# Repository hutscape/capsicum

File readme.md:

# Capsicum

> 🫑 Retrofit a wired doorbell to add WiFi and make it smart 🔔

Visit [hutscape.com/capsicum](https://hutscape.com/capsicum) for more details.

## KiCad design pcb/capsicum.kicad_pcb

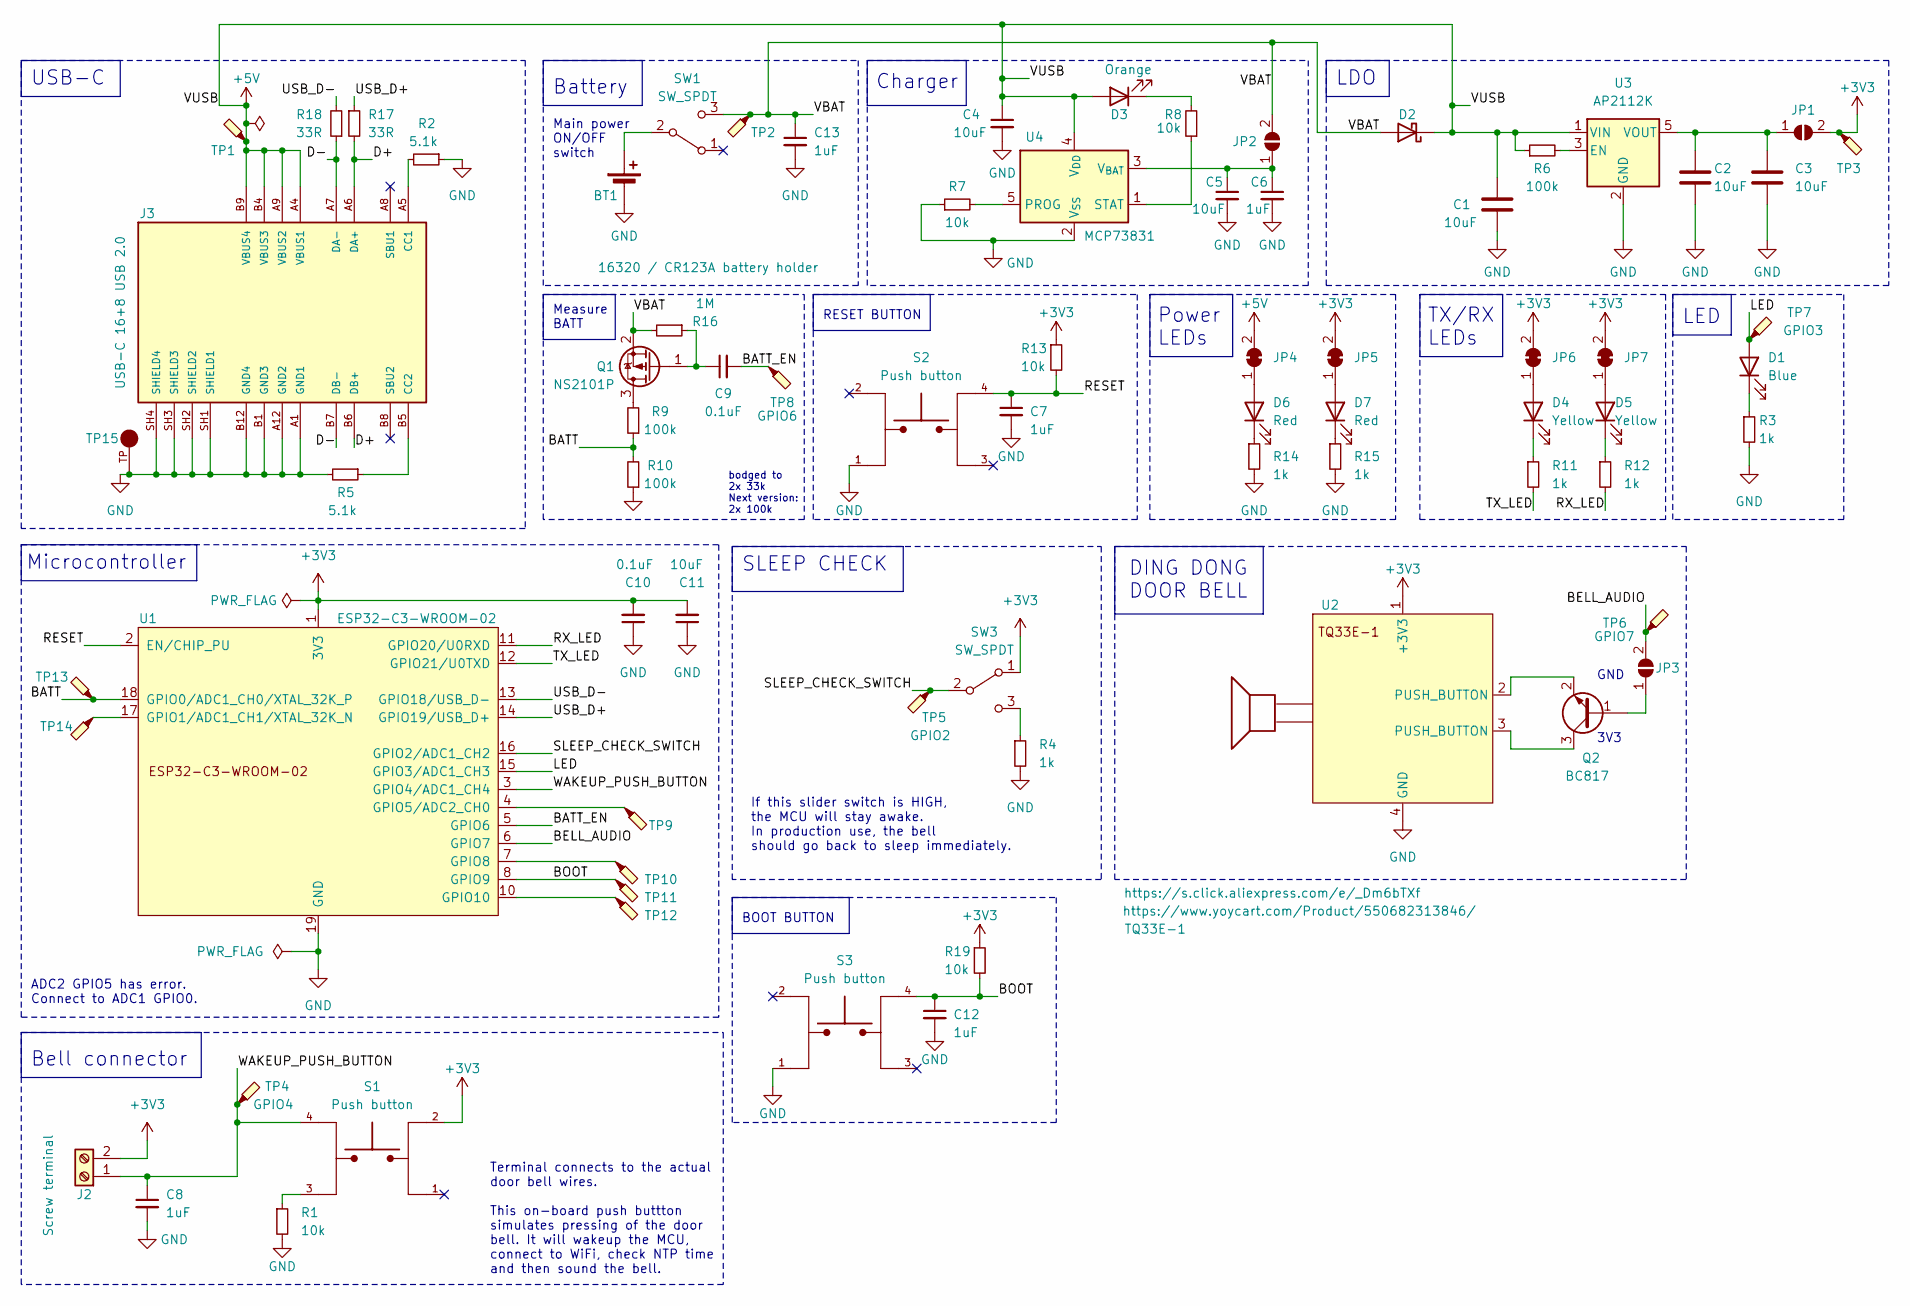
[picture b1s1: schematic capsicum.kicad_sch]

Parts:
BT1: 16320 / CR123A battery holder; CR123_holder
C1, C2, C3, C4, C5, C11: 10uF; C_0603_1608Metric; MPN CC0603KRX5R6BB106
C6, C7, C8, C12, C13: 1uF; C_0603_1608Metric; MPN 06033D105MAT2A
C9, C10: 0.1uF; C_0603_1608Metric; MPN 06033C104KAT4A
D1: Blue; D_0603_1608Metric; MPN 150060BS75000
D2: D_Schottky; D_SOD-123F; MPN PMEG3020EH,115
D3: Orange; D_0603_1608Metric; MPN B1911UD--20D001014U1930
D4, D5: Yellow; D_0603_1608Metric; MPN 150060YS75000
D6, D7: Red; D_0603_1608Metric; MPN 150060RS75000
J2: Screw terminal; phoenix_screw_terminal_th_1935161; MPN 1935161
J3: USB-C 16+8 USB 2.0; Molex_USB_C_2137160001; PARTREV B
JP1, JP2, JP3: SolderJumper_2_Open; PinHeader_1x02_P2.54mm_Vertical; MPN 61300211121
JP4, JP5, JP6, JP7: SolderJumper_2_Bridged; SolderJumper-2_P1.3mm_Bridged_RoundedPad1.0x1.5mm
Q1: NS2101P; SOT-323_SC-70; MPN NTS2101PT1G
Q2: BC817; SOT-23-3; MPN BC817-16LT3G
R1, R7, R8, R13, R19: 10k; R_0603_1608Metric; MPN RC0603FR-0710KL
R2, R5: 5.1k; R_0603_1608Metric; MPN ERJ-3GEYJ512V
R3, R4, R11, R12, R14, R15: 1k; R_0603_1608Metric; MPN RC0603FR-071KL
R6, R9, R10: 100k; R_0603_1608Metric; MPN RMCF0603FT100K
R16: 1M; R_0603_1608Metric; MPN RC0603FR-071ML
R17, R18: 33R; R_0603_1608Metric; MPN RC0603JR-0733RL
S1, S2, S3: Push button; SW_TL3305AF160QG; PARTREV C
SW1: SW_SPDT; SW_SPDT_PCM12; MPN CUS-12TB
SW3: SW_SPDT; SW_JS102011JCQN; MPN JS102011JCQN
TP1, TP2, TP3, TP4, TP5, TP6, TP7, TP8, TP9, TP10, TP11, TP12, TP13, TP14: TestPoint_Probe; TestPoint_Pad_1.5x1.5mm
TP15: 5015; Keystone_test_point_5015; MPN 5015
U1: ESP32-C3-WROOM-02; MPN ESP32-C3-WROOM-02-N4
U2: R/A 4x1 2.54mm pin header; PinHeader_1x04_P2.54mm_Horizontal; MPN PH1RB-04-UA
U3: AP2112K; SOT-23-5; MPN AP2112K-3.3TRG1
U4: MCP73831; SOT-23-5; MPN MCP73831T-2ACI/OT

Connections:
+3V3: C10.2, C11.2, J2.2, JP1.2 (B), JP5.2 (B), JP6.2 (B), JP7.2 (B), R13.1, R19.1, S1.2, SW3.1 (A), TP3.1, U1.1 (3V3), U2.1 (+3V3)
+5V: C1.1, C4.1, D2.1 (K), D3.2 (A), J3.A4 (VBUS1), J3.A9 (VBUS2), J3.B4 (VBUS3), J3.B9 (VBUS4), JP4.2 (B), R6.1, TP1.1, U3.1 (VIN), U4.4 (V_{DD})
/BATT: R9.1, R10.2, TP13.1, U1.18 (GPIO0/ADC1_CH0/XTAL_32K_P)
/BATT_EN: C9.2, TP8.1, U1.5 (GPIO6)
/BELL_AUDIO: JP3.2 (B), TP6.1, U1.6 (GPIO7)
/BOOT: C12.1, R19.2, S3.4, TP11.1, U1.8 (GPIO9)
/D+: J3.A6 (DA+), J3.B6 (DB+), R17.2
/D-: J3.A7 (DA-), J3.B7 (DB-), R18.1
/LED: D1.2 (A), TP7.1, U1.15 (GPIO3/ADC1_CH3)
/RESET: C7.1, R13.2, S2.4, U1.2 (EN/CHIP_PU)
/RX_LED: R12.2, U1.11 (GPIO20/U0RXD)
/SLEEP_CHECK_SWITCH: SW3.2 (B), TP5.1, U1.16 (GPIO2/ADC1_CH2)
/TX_LED: R11.2, U1.12 (GPIO21/U0TXD)
/USB_D+: R17.1, U1.14 (GPIO19/USB_D+)
/USB_D-: R18.2, U1.13 (GPIO18/USB_D-)
/VBAT: C13.1, D2.2 (A), JP2.2 (B), Q1.2 (S), R16.2, SW1.3 (C), TP2.1
/WAKEUP_PUSH_BUTTON: C8.1, J2.1, S1.4, TP4.1, U1.3 (GPIO4/ADC1_CH4)
GND: BT1.2 (-), C1.2, C2.2, C3.2, C4.2, C5.2, C6.2, C7.2, C8.2, C10.1, C11.1, C12.2, C13.2, J3.A1 (GND1), J3.A12 (GND2), J3.B1 (GND3), J3.B12 (GND4), J3.SH1 (SHIELD1), J3.SH2 (SHIELD2), J3.SH3 (SHIELD3), J3.SH4 (SHIELD4), R1.2, R2.1, R3.2, R4.2, R5.2, R7.1, R10.1, R14.2, R15.2, S2.1, S3.1, TP15.TP, U1.9 (GND), U1.19 (GND), U2.4 (GND), U3.2 (GND), U4.2 (V_{SS})
unnamed: BT1.1 (+), SW1.2 (B)
unnamed: D1.1 (K), R3.1
unnamed: D3.1 (K), R8.2
unnamed: D4.2 (A), JP6.1 (A)
unnamed: D4.1 (K), R11.1
unnamed: D5.2 (A), JP7.1 (A)
unnamed: D5.1 (K), R12.1
unnamed: D6.2 (A), JP4.1 (A)
unnamed: D6.1 (K), R14.1
unnamed: D7.2 (A), JP5.1 (A)
unnamed: D7.1 (K), R15.1
unnamed: J3.A5 (CC1), R2.2
unnamed: J3.B5 (CC2), R5.1
unnamed: C2.1, C3.1, JP1.1 (A), U3.5 (VOUT)
unnamed: C5.1, C6.1, JP2.1 (A), U4.3 (V_{BAT})
unnamed: JP3.1 (A), Q2.1 (B)
unnamed: Q1.3 (D), R9.2
unnamed: C9.1, Q1.1 (G), R16.1
unnamed: Q2.3 (C), U2.3 (PUSH_BUTTON)
unnamed: Q2.2 (E), U2.2 (PUSH_BUTTON)
unnamed: R1.1, S1.3
unnamed: R4.1, SW3.3 (C)
unnamed: TP14.1, U1.17 (GPIO1/ADC1_CH1/XTAL_32K_N)
unnamed: TP9.1, U1.4 (GPIO5/ADC2_CH0)
unnamed: TP10.1, U1.7 (GPIO8)
unnamed: TP12.1, U1.10 (GPIO10)
unnamed: R6.2, U3.3 (EN)
unnamed: R7.2, U4.5 (PROG)
unnamed: R8.1, U4.1 (STAT)

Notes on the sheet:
LED
Terminal connects to the actual door bell wires. This on-board push buttton simulates pressing of the door bell. It will wakeup the MCU, connect to WiFi, check NTP time and then sound the bell.
TX/RX LEDs
bodged to 2x 33k Next version: 2x 100k
Main power ON/OFF switch
If this slider switch is HIGH, the MCU will stay awake. In production use, the bell should go back to sleep immediately.
3V3
Measure BATT
SLEEP CHECK
ADC2 GPIO5 has error. Connect to ADC1 GPIO0.
RESET BUTTON
Charger
BOOT BUTTON
USB-C
Bell connector
DING DONG DOOR BELL
Microcontroller
GND
Power LEDs
Battery
LDO

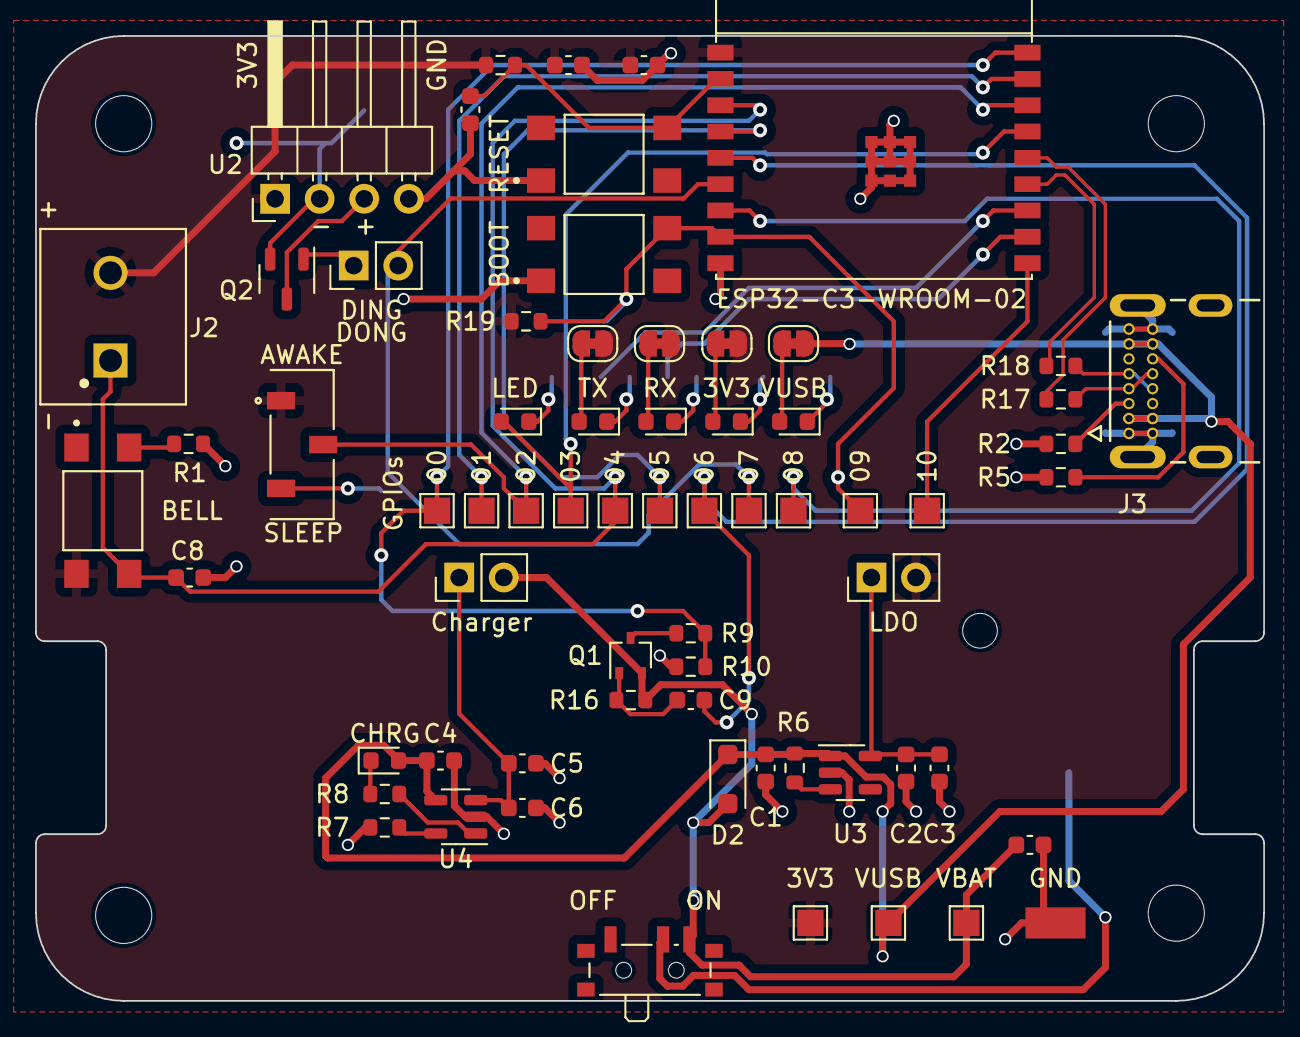
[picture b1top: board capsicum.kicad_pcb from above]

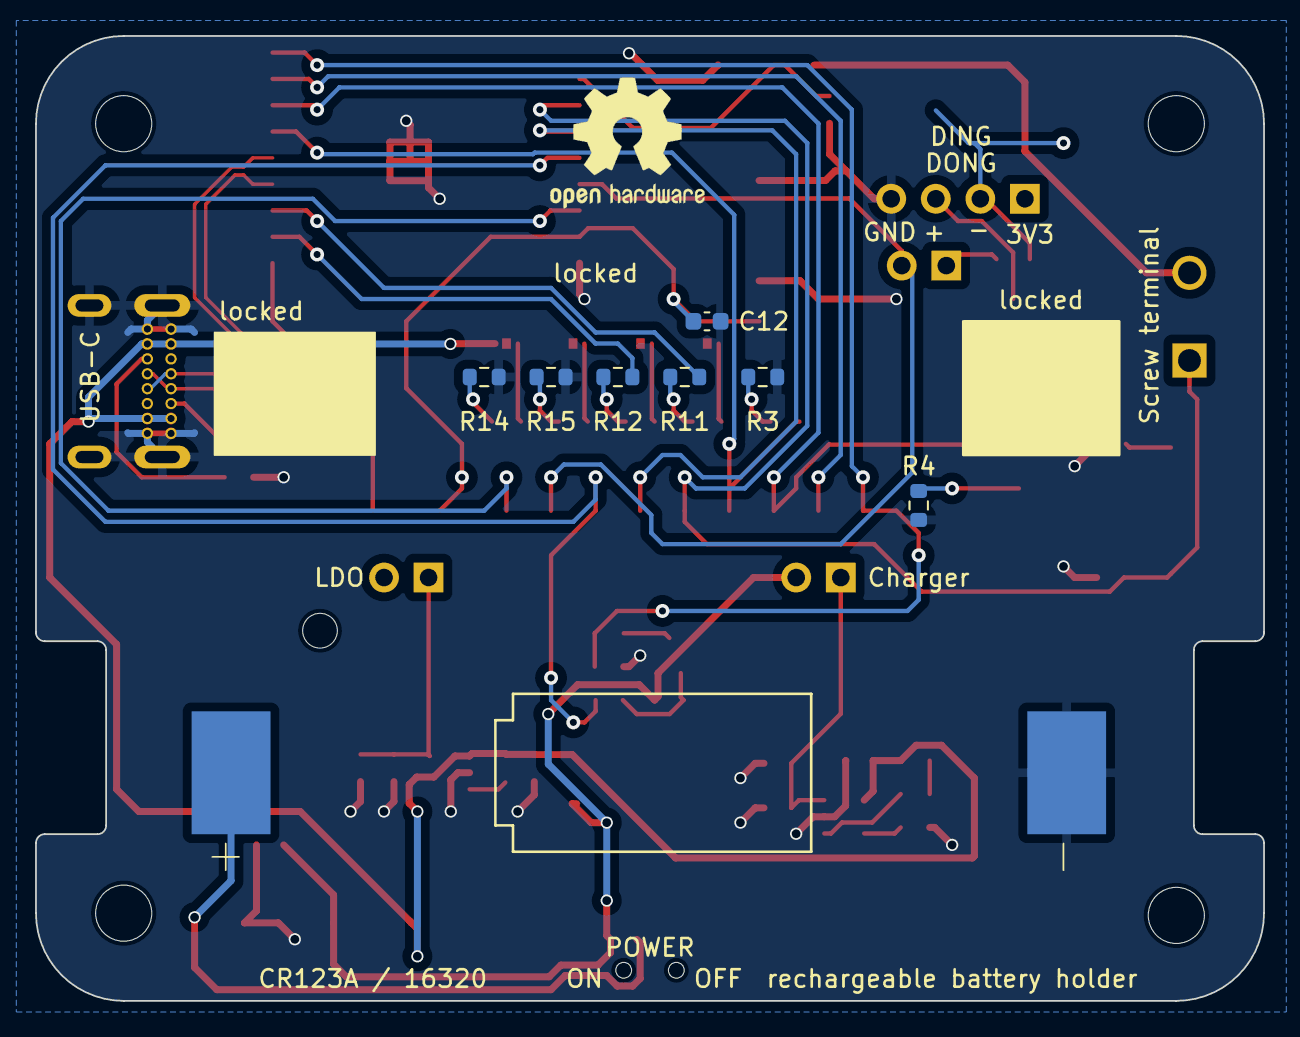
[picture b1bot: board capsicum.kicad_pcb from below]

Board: 2 copper layers, 70.0 x 55.0 mm, 75 parts (8 on the bottom side), 47 nets.

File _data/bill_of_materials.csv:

Designator,Value,Qty,Package,Category,Manufacturer,MPN,Datasheet,Vendor,Link,Unit,Total,Description,DNP
BT1,16320 / CR123A battery holder,1,SMD,Connector,EAEONXE,,https://www.aliexpress.com/item/1005004821679671.html,AliExpress,https://s.click.aliexpress.com/e/_DBxLGXX,2.2200,2.2200,Battery Holder CR123A:CR123_holder,
"C1-C5, C11",10uF,6,0603,Electronics,YAGEO,CC0603KRX5R6BB106,https://www.yageo.com/upload/website/yageo_High%20Capacitanc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,PCBWay,https://www.digikey.sg/en/products/detail/yageo/CC0603KRX5R6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,0.0284,0.1704,Capacitor_SMD:C_0603_1608Metric,
"C6-C8, C12, C13",1uF,5,0603,Electronics,Kyocera,06033D105MAT2A,https://datasheets.kyocera-avx.com/cx5r.pdf,PCBWay,https://www.digikey.co.nz/en/products/detail/kyocera-avx/KGM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,0.1748,0.8740,Capacitor_SMD:C_0603_1608Metric,
"C9, C10",0.1uF,2,0603,Electronics,Kyocera,06033C104KAT4A,https://datasheets.kyocera-avx.com/X7RDielectric.pdf,PCBWay,https://www.digikey.ca/en/products/detail/kyocera-avx/KGM15B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,0.1028,0.2056,Capacitor_SMD:C_0603_1608Metric,
D1,Blue,1,0603,Electronics,Würth Elektronik,150060BS75000,https://www.we-online.com/components/products/datasheet/1500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,PCBWay,https://www.digikey.sg/en/products/detail/w%C3%BCrth-elektro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,0.1970,0.1970,Diode_SMD:D_0603_1608Metric,
D2,D_Schottky,1,SOD-123F,Electronics,Nexperia USA Inc.,"PMEG3020EH,115",https://assets.nexperia.com/documents/data-sheet/PMEG3020EH.pdf,PCBWay,https://www.digikey.sg/en/products/detail/nexperia-usa-inc/P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,0.5566,0.5566,Diode_SMD:D_SOD-123F,
D3,Orange,1,0603,Electronics,Harvatek Corporation,B1911UD--20D001014U1930,https://mm.digikey.com/Volume0/opasdata/d220001/medias/docus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,PCBWay,https://www.digikey.sg/en/products/detail/harvatek-corporati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,0.1199,0.1199,Diode_SMD:D_0603_1608Metric,
"D4, D5",Yellow,2,0603,Electronics,Würth Elektronik,150060YS75000,https://www.we-online.com/components/products/datasheet/1500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,PCBWay,https://www.digikey.sg/en/products/detail/w%C3%BCrth-elektro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,0.1790,0.3580,Diode_SMD:D_0603_1608Metric,
"D6, D7",Red,2,0603,Electronics,Würth Elektronik,150060RS75000,https://www.we-online.com/components/products/datasheet/1500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,PCBWay,https://www.digikey.sg/en/products/detail/w%C3%BCrth-elektro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,0.1790,0.3580,Diode_SMD:D_0603_1608Metric,
J2,Screw terminal,1,TH,Connector,Phoenix,1935161,https://media.digikey.com/pdf/Data%20Sheets/Phoenix%20Contac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,PCBWay,https://www.digikey.sg/en/products/detail/phoenix-contact/19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,0.2835,0.2835,Screw Terminal:phoenix_screw_terminal_th_1935161,
J3,USB-C 16+8 USB 2.0,1,TH,Connector,Molex,2137160001,https://www.molex.com/en-us/products/part-detail/2137160001,PCBWay,https://www.digikey.sg/en/products/detail/molex/2137160001/13662558,0.9651,0.9651,Molex_USB_C:Molex_USB_C_2137160001,
JP1-JP3,SolderJumper_2_Open,3,TH,Electronics,Würth Elektronik,61300211121,https://www.we-online.com/components/products/datasheet/6130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,PCBWay,https://www.digikey.sg/en/products/detail/w%C3%BCrth-elektro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,0.0945,0.2835,Connector_PinHeader_2.54mm:PinHeader_1x02_P2.54mm_Vertical,
JP4-JP7,SolderJumper_2_Bridged,4,,Electronics,,,,,,0.0000,0.0000,Jumper:SolderJumper-2_P1.3mm_Bridged_RoundedPad1.0x1.5mm,DNP all
Q1,NS2101P,1,SC-70-3 (SOT323),Electronics,OnSemi,NTS2101PT1G,https://www.onsemi.com/pdf/datasheet/nts2101p-d.pdf,PCBWay,https://www.digikey.sg/en/products/detail/onsemi/NTS2101PT1G/687099,0.4712,0.4712,Package_TO_SOT_SMD:SOT-323_SC-70,
Q2,BC817,1,SOT-23-3,Electronics,OnSemi,BC817-16LT3G,https://www.onsemi.com/pub/Collateral/BC818-D.pdf,PCBWay,https://www.digikey.sg/en/products/detail/onsemi/BC817-16LT3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,0.1593,0.1593,Package_TO_SOT_SMD:SOT-23-3,
"R1, R7, R8, R13, R19",10k,5,0603,Electronics,YAGEO,RC0603FR-0710KL,https://www.yageo.com/upload/media/product/productsearch/dat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,PCBWay,https://www.digikey.sg/en/products/detail/yageo/RC0603FR-071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,0.0038,0.0190,Resistor_SMD:R_0603_1608Metric,
"R2, R5",5.1k,2,0603,Electronics,Panasonic,ERJ-3GEYJ512V,https://industrial.panasonic.com/ww/products/pt/general-purp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,PCBWay,https://www.digikey.sg/en/products/detail/panasonic-electron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,0.1149,0.2298,Resistor_SMD:R_0603_1608Metric,
"R3, R4, R11, R12, R14, R15",1k,6,0603,Electronics,Yageo,RC0603FR-071KL,https://www.yageo.com/upload/media/product/productsearch/dat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,PCBWay,https://www.digikey.sg/en/products/detail/yageo/RC0603FR-071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,0.1149,0.6894,Resistor_SMD:R_0603_1608Metric,
"R6, R9, R10",100k,3,0603,Electronics,Stackpole,RMCF0603FT100K,https://www.seielect.com/Catalog/SEI-RMCF_RMCP.pdf,PCBWay,https://www.digikey.sg/en/products/detail/stackpole-electron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,0.1149,0.3447,Resistor_SMD:R_0603_1608Metric,
R16,1M,1,0603,Electronics,YAGEO,RC0603FR-071ML,https://www.yageo.com/upload/media/product/productsearch/dat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,PCBWay,https://www.digikey.sg/en/products/detail/yageo/RC0603FR-071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,0.0013,0.0013,Resistor_SMD:R_0603_1608Metric,
"R17, R18",33R,2,0603,Electronics,YAGEO,RC0603JR-0733RL,https://www.yageo.com/upload/media/product/productsearch/dat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,PCBWay,https://www.digikey.sg/en/products/detail/yageo/RC0603JR-073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,0.0208,0.0416,Resistor_SMD:R_0603_1608Metric,
S1-S3,Push button,3,SMD,Connector,E-Switch,TL3305AF160QG,https://sten-eswitch-13110800-production.s3.amazonaws.com/sy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,PCBWay,https://www.digikey.sg/en/products/detail/e-switch/TL3305AF1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,0.1701,0.5103,Push button:SW_TL3305AF160QG,
SW1,SW_SPDT,1,SMD,Electronics,Nidec Copal,CUS-12TB,https://www.nidec-components.com/e/catalog/switch/cus.pdf,PCBWay,https://www.digikey.sg/en/products/detail/nidec-copal-electr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,0.8033,0.8033,Button_Switch_SMD:SW_SPDT_PCM12,
SW3,SW_SPDT,1,SMD,Electronics,C&K,JS102011JCQN,https://www.ckswitches.com/media/1422/js.pdf,PCBWay,https://www.digikey.sg/en/products/detail/c-k/JS102011JCQN/6137628,0.7125,0.7125,Slide switch:SW_JS102011JCQN,
TP1-TP14,TestPoint_Probe,14,,Electronics,,,,,,0.0000,0.0000,TestPoint:TestPoint_Pad_1.5x1.5mm,DNP all
TP15,5015,1,SMD,Electronics,Keystone,5015,https://www.keyelco.com/userAssets/file/M65p55.pdf,PCBWay,https://www.digikey.sg/en/products/detail/keystone-electroni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,0.1418,0.1418,Keystone_TP:Keystone_test_point_5015,
U1,ESP32-C3-WROOM-02,1,SMD,Electronics,Espressif,ESP32-C3-WROOM-02-N4,https://www.espressif.com/sites/default/files/documentation/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,PCBWay,https://www.digikey.sg/en/products/detail/espressif-systems/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,2.6334,2.6334,Espressif:ESP32-C3-WROOM-02,
U2,R/A 4x1 2.54mm pin header,1,TH,Electronics,Adam Tech,PH1RB-04-UA,https://app.adam-tech.com/products/download/data_sheet/20128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,PCBWay,https://www.digikey.sg/en/products/detail/adam-tech/PH1RB-04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,0.2600,0.2600,Connector_PinHeader_2.54mm:PinHeader_1x04_P2.54mm_Horizontal,
U3,AP2112K,1,SOT-23-5 or SOT-753 or SOT-25,Electronics,Diodes Incorporated,AP2112K-3.3TRG1 ,https://www.diodes.com/assets/Datasheets/AP2112.pdf,PCBWay,https://www.digikey.sg/en/products/detail/diodes-incorporate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,0.1985,0.1985,Package_TO_SOT_SMD:SOT-23-5,
U4,MCP73831,1,SOT-23-5,Electronics,Microchip,MCP73831T-2ACI/OT,https://ww1.microchip.com/downloads/en/DeviceDoc/MCP73831-Fa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,PCBWay,https://www.digikey.sg/en/products/detail/microchip-technolo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,0.8701,0.8701,Package_TO_SOT_SMD:SOT-23-5,

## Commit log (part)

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2022-04-13 docs: add description
2022-04-13 feat: add initial content for project capsicum
2022-04-13 refactor: remove unused version
2022-04-20 "refactor: sync status tags and update footer"
2022-04-20 "refactor: put the download links first on the start page"
2022-04-21 "feat: add new git submodule and install themupon creating new project"
2022-04-21 feat: add image on the batteries used
2022-04-21 "refactor: seperate Design page into more partials"
2022-05-13 "feat: add VSCode text editor and FreeCAD files to gitignore"
2022-05-19 "feat: add /case layout for projects with enclosure designs"
2022-07-21 "fix: change link to code images"
2022-07-22 "fix: change GitHub URL for HTML code examples"
2022-07-22 chore: move images from hardware to pcb directory
2022-07-22 fix: turn off downloads section
2022-11-02 feat: add wifi scan example code
2022-11-08 fix: move tutorial to another repo
2022-11-13 refactor: move connect wifi code to anoher repo
2023-10-23 chore: update dependancies
2023-10-23 docs: add more reference projects
2023-10-25 docs: add more information about prospective parts
2023-10-26 docs: add subsystem design diagram
2023-10-28 chore: update gitsubmodules
2023-11-10 refactor: change to OOP style
2023-11-10 feat: add wakeup and sleep to ring the bell
2023-11-11 feat: remain awake if the sleep check gpio pin is HIGH
2023-11-12 feat: add NTP time check to ring the bell within the time range
2023-11-12 refactor: reduce bell timing
2023-11-12 chore: add TODO tasks
2023-11-14 feat: add debug print statemetns
2023-11-14 feat: add debug print to ntp time manager
2023-11-14 refactor: add debug prints
2023-11-15 docs: add potential parts for subwoofer speaker
2023-11-15 docs: add updated image of the demo code schematic
2023-11-18 fix: fix currentHour check with NTP Time to ring the bell
2023-11-18 refactor: enable Zapier
2023-11-20 refactor: comment sending webhook to Zapier to saty under the free plan limit
2023-11-20 fix: change extract hour from 12 hour to 24 hour
2023-11-23 feat: new demo code with KiCad schematic with TQE33-1 bell audio chip
2023-11-28 feat: add components in the schematic
2023-11-29 feat: add bell connector to the schematic
2023-11-29 feat: associate 0603 capcitors and resistors footprints
2023-12-04 refactor: add battery measurement circuit that saves power draw
2023-12-06 feat: associate push buttons and slide switches to MPN and footprints
2023-12-07 feat: associate USB-C through-hole 16+8 USB2.0 connector footprint
2023-12-08 feat: add test points and bridged jumpers
2023-12-10 docs: add links on low power batt measurement circuit
2023-12-11 docs: change URL for buying the wired doorbell
2023-12-12 feat: associate MPN and BOM details for orange LED in charging circuit
2023-12-12 feat: associate MPN and BOM details for red LED in charging circuit
2023-12-12 feat: associate MPN and BOM details for some resistor values
2023-12-14 refactor: udpate bell ding dong chip to integrate the speaker
2023-12-15 feat: publish bill of materials
2023-12-25 feat: add right-angled header pin connector for the bell
2023-12-25 fix: fix bom cost code
2023-12-27 feat: reorient all text to face upright on silkscreen layer
2023-12-30 feat: group components from batt measurement logical block in layout
2023-12-30 feat: group components from LDO logical block in layout
2023-12-30 feat: group components from power LEDs logical block in layout
2023-12-30 feat: group components from sleep-check logical block in layout
2023-12-30 feat: group components from bell connector logical block in layout
2023-12-31 feat: update layout, schematic and BOM with new test point for ground
2024-01-01 feat: replace 3x open jumpers with solderless option of header pins for jumper caps
2024-01-03 feat: add silkscreen text about project
2024-01-03 docs: add notes for snap-fit 3d printed enclosures
2024-01-04 feat: place components for case groves-teeth and mounting holes
2024-01-05 feat: add C&K Slide switch SPDT 3D model and footprint
2024-01-09 feat: add grid origin and pcb dimensions in User.Drawings layer
2024-01-23 feat: import KiCAD PCB into FreeCAD
2024-01-23 fix: remove long DNP in BOM
2024-01-23 feat: make a cuboid to house the pcb
2024-01-23 feat: cut connector and LED slots
2024-01-24 refactor: reduce LED slot width
2024-01-24 feat: add 4x screw supports
2024-01-24 feat: fix ventilation hole cut operation
2024-01-25 feat: fuse round speaker base
2024-01-25 feat: add battery 3D model to battery holder
2024-01-25 feat: integrate speaker 3D Model and STL exports
2024-01-25 feat: create a seperation plane to avoid the protruding screw supports
2024-01-25 refactor: move the speaker plot higher up to not clash with ESP32C3 board
2024-01-26 feat: add 4x teeth
2024-01-26 feat: add 4x grooves
2024-01-26 refactor: change board shape to make way for teeth and groove
2024-01-26 refactor: move LEDs, USB-C and Screw terminal connectors in PCB layout
2024-01-30 refactor: move LED slot
2024-01-31 feat: drop power fill zones on top and bottom layers [119 unconnected]
2024-01-31 feat: add traces to battery logic block [110 unconected]
2024-01-31 feat: add traces to charger logic block [96 unconnected]
2024-01-31 feat: add traces to batt measurement logic block [75 unconnected]
2024-01-31 feat: add traces to LED logic blocks [54 unconnected]
2024-01-31 feat: add traces to bell audio logic block [49 unconnected]
2024-01-31 feat: add traces to bell logic block [40 unconnected]
2024-01-31 docs: export new layout and schematic
2024-01-31 refactor: move notes in back silkscreen
2024-02-01 refactor: move LED slot and import pcb in FreeCAD
2024-02-01 feat: connect all power unconnected power zones [12 unconnected]
2024-02-01 feat: connect more traces [1 unconnected]
2024-02-01 docs: update all images and exports
2024-02-02 feat: add project name and LED text
2024-02-02 docs: export images and STL files
2024-02-06 refactor: rename 5V to VUSB
2024-02-08 docs: add photos of new doorbell
2024-02-08 docs: regenerate all docs after adding new capacitor and VUSB label
2024-02-16 docs: add case width and length distances in FreeCAD
2024-02-16 feat: add a configurable timeout for the bell to ring
2024-02-16 refactor: move silkscreen Notes and Install Date to a position that is wrtable
2024-02-19 refactor: update debug message to print the length of bell timeout
2024-02-20 docs: add lessons for V2.0 iteration
2024-02-26 feat: add layout for listing manufacturing params and image
2024-02-26 fix: change uniq parts to 30 due to off-by-one error
2024-02-26 fix: add missing vendor name in BOM for PCB Assembly
2024-02-27 fix: change all LED and diode to the correct footprint with polarity markings
2024-02-27 docs: link to generated gerbers
2024-02-29 chore: update submodule to seperate case page into sections
2024-02-29 docs: add specific MPN for ESP32-C3
2024-03-04 feat: display all prototype images until defined max_prototype_images
2024-03-13 feat: add interactive HTML BOM
2024-03-13 docs: update monthly progress notes
2024-03-15 feat: add software bill of materials
2024-03-17 docs: add RGB LED for V2 and update submodule
2024-03-20 docs: add V2 iteration improvements on OTA
2024-03-20 docs: add V2 iteration improvements on a better quality slide switch
2024-03-25 docs: add resources to flash a raw ESP32-C3-WROOM-02
2024-03-26 docs: add improvement and schedule
2024-03-27 docs: add notes on GitHub release with new tag
2024-03-27 feat: add blinky code for PCB
2024-03-27 refactor: divide others page into csq and resources
2024-03-29 chore: update submodule to remove unused Others page
2024-03-29 docs: generate new iBom
2024-04-01 feat: add demo breadboard and demo PCB code
2024-04-01 docs: add images for demo code
2024-04-01 chore: update submodules to hyperlink images
2024-04-01 feat: add a section on photos of manufactured PCBs
2024-04-04 docs: add a todo comment to remove Serial.begin and while loop for production
2024-04-04 docs: add improvements for next version
2024-04-04 docs: add images for blinky code
2024-04-06 feat (firmware): add options in Makefile and demo.ino for production build
2024-04-06 refactor (firmware): add power consumption optimisation code
2024-04-09 docs: add power consumption measurement file downloads
2024-04-09 docs (firmware): add todo tasks for battery level calculation and send to Zapier
2024-04-09 chore: refactor Makefile to exclude TODO comments from cpplint
2024-04-09 docs: fix typo in comment for sending to Zapier in production environment
2024-04-10 feat (firmware): add environment information in webhook config
2024-04-10 refactor (firmware): handle unavailable port in Makefile target upload
2024-04-11 feat: add a new power page
2024-04-11 fix: change hyperlinks to PPK2 file downloads
2024-04-11 refactor (firmware): simplify web server client for reading batt voltage
2024-04-12 chore: update submodules to upgrade to latest JS and CSS libraries
2024-04-12 refactor: simply putting content on start page with only Markdown
2024-04-12 docs (power): add falstad battery measurement circuit simulation
2024-04-12 fix: change datasheet link for p-channel mosfet NTS2101P
2024-04-15 docs (power): add resistors 100k in simulation for batt measurement
2024-04-15 docs (power): update link to web archive
2024-04-16 Update issue templates
2024-05-02 docs: update lessons and resources for next version
2024-05-04 chore: update submodules to add a link to download demo code
2024-05-06 refactor (docs): simplify iteration ideas into one big list
2024-06-15 docs: add todo task for blinking LED for low battery level
2024-06-19 fix (firmware): remove unnecessary delay in loop function to measure batt level
2024-06-19 feat (firmware): add battery level percentage value
2024-06-19 refactor (firmware): remove undefined variable and function in access point example
2024-06-20 feat (firmware): improve access point code example with WiFi connection instructions and webpage screenshot
2024-06-23 docs (power): add links to battery measurement circuit and code
2024-07-09 fix (firmware, schematic, layout): change vref for adc and resistors to measure battery voltage
2024-07-09 refactor (firmware): increase the accuracy of Vref to 2.86V
2024-07-11 docs (firmware): add oscilloscope screenshots for measuring batt voltage
2024-07-12 feat (firmware): update battery level calculation and pin assignments
2024-07-13 chore: update Gemfile
2024-10-11 chore: update submodule to add checkboxes to Feature list
2024-10-11 feat: update WiFiConnector timeout to 2 seconds to fallback to ringing the bell like normal
2024-11-02 feat (prototype): Add example for testing retrofit of doorbell with only breadboard and PSU
2024-11-13 feat (firmware): add tutorial on using minimum code with dev board and breadboard
2024-11-13 refactor (firmware): remove the print wakeup reason function to make the code even more minimal
2024-11-13 docs: add project name reasoning
2024-11-14 chore: update submodule to display the rationale of the project name
2024-11-14 feat: add user labels for buttons and power connections in PCB and schematic
2024-11-15 feat (firmware): update LEDController to support customizable blink period
2024-11-15 fix: update debug message to reflect bell mute status and correct environment variable assignment
2024-11-18 fix (firmware): ensure batt level is sent to the post hook
2024-11-18 refactor (firmware): remove environment variable from webhook configuration
2024-12-04 feat (firmware): add demo code for measuring raw ADC value on ESP32-C3
2024-12-05 fix (firmware): initialize LED controller before blinking for low battery warning
2024-12-05 refactor (firmware): enhance time range check logging for better clarity
2024-12-06 refactor (firmware): update debug levels and enhance logging for time management and battery alerts
2024-12-06 fix (documentation): correct indentation and add serial console image
2024-12-11 chore: generate updated schematic, layout, iBOM
2024-12-13 fix (documentation): update lessons for layout, case, and firmware improvements
2024-12-24 chore: update config to exclude _code directory from processing
2024-12-24 chore: update kicad and scripts

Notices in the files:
pcb/capsicum.kicad_pcb:
License: CC-BY-SA 4.0 or TAPR
